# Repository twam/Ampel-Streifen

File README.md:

Ampel-Streifen – Traffic Light LED Strip
===

[![CC BY-SA 4.0][cc-by-sa-shield]][cc-by-sa]

This work is licensed under a [Creative Commons Attribution-NonCommercial-ShareAlike 4.0 International License][cc-by-sa].

[![CC BY-SA 4.0][cc-by-sa-image]][cc-by-sa]

[cc-by-sa]: http://creativecommons.org/licenses/by-nc-sa/4.0/
[cc-by-sa-image]: https://licensebuttons.net/l/by-nc-sa/4.0/88x31.png
[cc-by-sa-shield]: https://img.shields.io/badge/License-CC%20BY--NC--SA%204.0-lightgrey.svg

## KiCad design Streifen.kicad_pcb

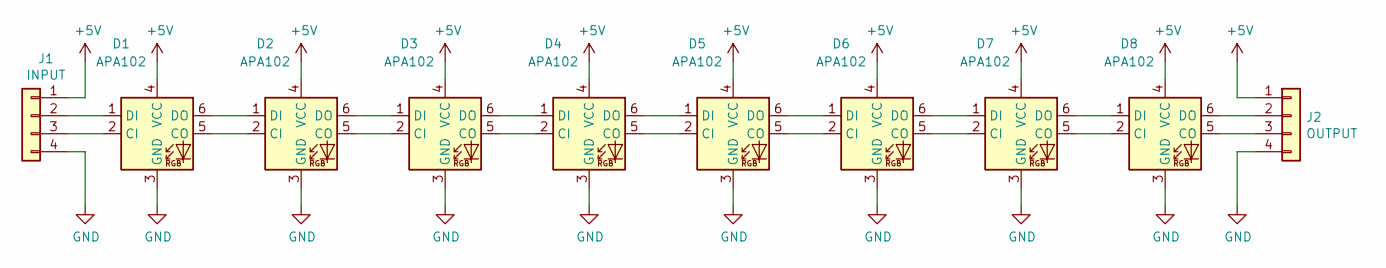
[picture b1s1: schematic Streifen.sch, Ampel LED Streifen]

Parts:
D1, D2, D3, D4, D5, D6, D7, D8: APA102; LED_RGB_5050-6
J1: INPUT; PinHeader_1x04_P2.54mm_Vertical
J2: OUTPUT; PinHeader_1x04_P2.54mm_Vertical

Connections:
+5V: D1.4 (VCC), D2.4 (VCC), D3.4 (VCC), D4.4 (VCC), D5.4 (VCC), D6.4 (VCC), D7.4 (VCC), D8.4 (VCC), J1.1, J2.1
GND: D1.3 (GND), D2.3 (GND), D3.3 (GND), D4.3 (GND), D5.3 (GND), D6.3 (GND), D7.3 (GND), D8.3 (GND), J1.4, J2.4
unnamed: D1.1 (DI), J1.2
unnamed: D1.2 (CI), J1.3
unnamed: D1.5 (CO), D2.2 (CI)
unnamed: D1.6 (DO), D2.1 (DI)
unnamed: D2.5 (CO), D3.2 (CI)
unnamed: D2.6 (DO), D3.1 (DI)
unnamed: D3.5 (CO), D4.2 (CI)
unnamed: D3.6 (DO), D4.1 (DI)
unnamed: D4.5 (CO), D5.2 (CI)
unnamed: D4.6 (DO), D5.1 (DI)
unnamed: D5.5 (CO), D6.2 (CI)
unnamed: D5.6 (DO), D6.1 (DI)
unnamed: D6.5 (CO), D7.2 (CI)
unnamed: D6.6 (DO), D7.1 (DI)
unnamed: D7.5 (CO), D8.2 (CI)
unnamed: D7.6 (DO), D8.1 (DI)
unnamed: D8.5 (CO), J2.3
unnamed: D8.6 (DO), J2.2

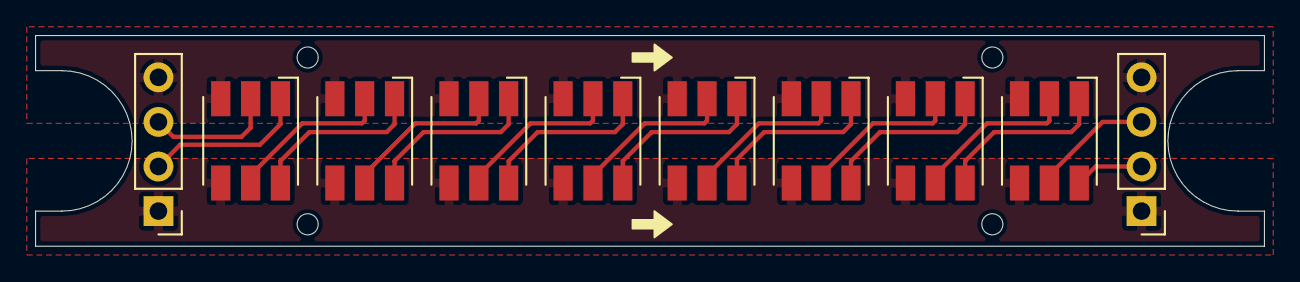
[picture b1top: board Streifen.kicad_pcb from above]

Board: 2 copper layers, 70.0 x 12.0 mm, 10 parts (0 on the bottom side), 20 nets.

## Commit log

2020-10-17 Add descriptions
2020-11-05 Add Readme
2020-11-11 Add STLs
